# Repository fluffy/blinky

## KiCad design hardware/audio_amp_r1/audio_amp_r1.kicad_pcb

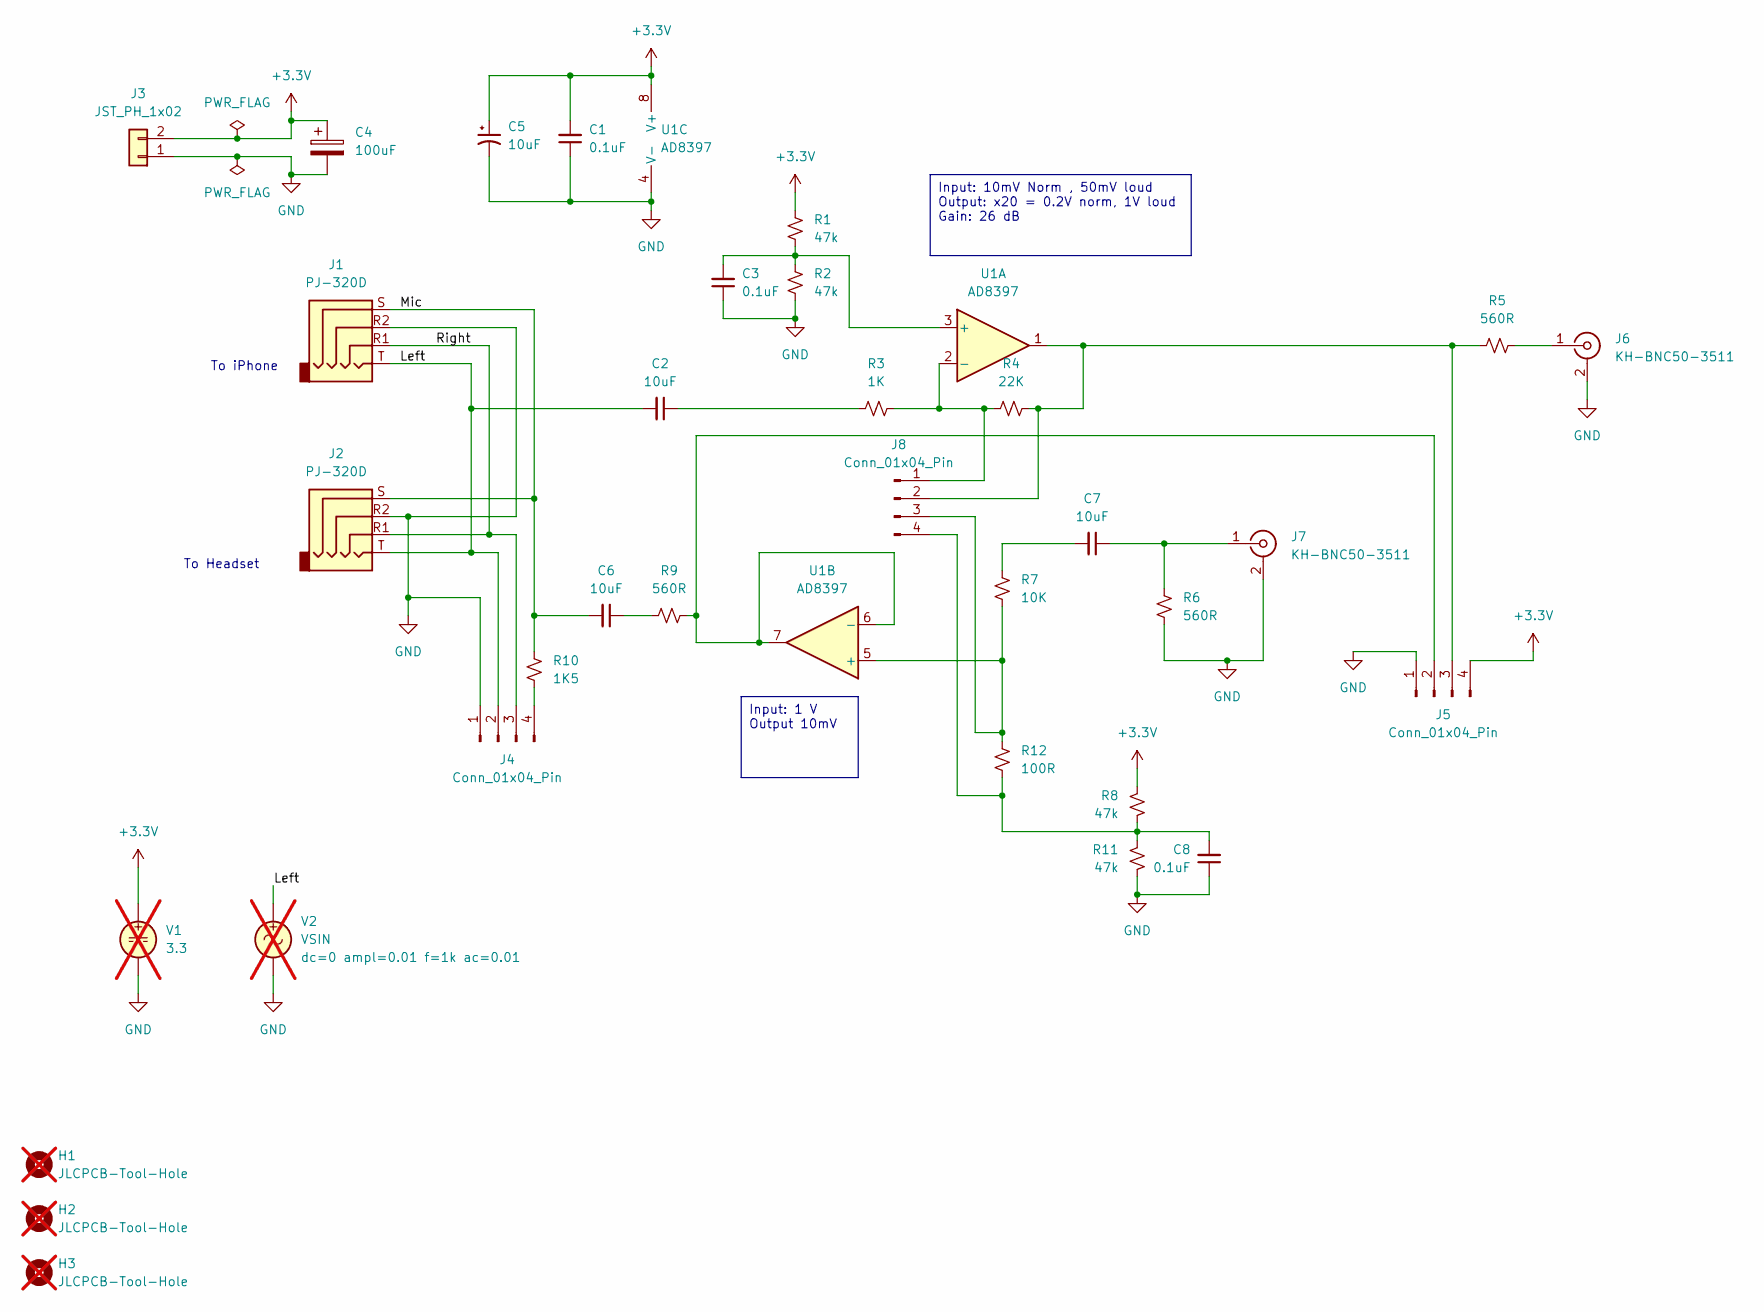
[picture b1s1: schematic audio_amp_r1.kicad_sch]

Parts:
C1, C3, C8: 0.1uF; C_0805_2012Metric; JLCPCB Part # C49678
C2, C6, C7: 10uF; C_0805_2012Metric; JLCPCB Part # C15850
C4: 100uF; CP_EIA-3528-21_Kemet-B; JLCPCB Part # C16133
C5: 10uF; CP_EIA-3216-18_Kemet-A; JLCPCB Part # C7171
H1, H2, H3: JLCPCB-Tool-Hole; MountingHole_JLCPCB_Tool; not fitted
J1, J2: PJ-320D; Jack_3.5mm_PJ320D_Horizontal-CJ; MPN PJ-320D; JLCPCB Part # C431535
J3: JST_PH_1x02; JST_PH_S2B-PH-SM4-TB_1x02-1MP_P2.00mm_Horizontal; JLCPCB Part # C295747
J4, J5, J8: Conn_01x04_Pin; PinHeader_1x04_P2.54mm_Vertical_SMD_Pin1Left; JLCPCB Part # C2883761
J6, J7: KH-BNC50-3511; BNC_Amphenol_B6252HB-NPP3G-50_Horizontal-CJ; MPN KH-BNC50-3511; JLCPCB Part # C2837587
R1, R2, R8, R11: 47k; R_0805_2012Metric; JLCPCB Part # C17713
R3: 1K; R_0805_2012Metric; JLCPCB Part # C17513
R4: 22K; R_0805_2012Metric; JLCPCB Part # C17560
R5, R6, R9: 560R; R_0805_2012Metric; JLCPCB Part # C28636
R7: 10K; R_0805_2012Metric; JLCPCB Part # C17414
R10: 1K5; R_0805_2012Metric; JLCPCB Part # C4310
R12: 100R; R_0805_2012Metric; JLCPCB Part # C17408
U1: AD8397; SOIC-8_3.9x4.9mm_P1.27mm; JLCPCB Part # C578714
V1: 3.3; not fitted
V2: VSIN; not fitted

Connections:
+3.3V: C1.2, C4.1, C5.1, J3.2, J5.4, R1.2, R8.2, U1.8 (V+), V1.1
/Left: C2.2, J1.T, J2.T, J4.2, V2.1
/Mic: C6.2, J1.S, J2.S, R10.2
/Right: J1.R1, J2.R1, J4.3
GND: C1.1, C3.1, C4.2, C5.2, C8.1, J1.R2, J2.R2, J3.1, J4.1, J5.1, J6.2 (Ext), J7.2 (Ext), R2.1, R6.2, R11.1, U1.4 (V-), V1.2, V2.2
unnamed: C2.1, R3.2
unnamed: C6.1, R9.1
unnamed: C7.2, R7.1
unnamed: J4.4, R10.1
unnamed: J5.2, R9.2, U1.6 (-), U1.7
unnamed: J5.3, J8.2, R4.1, R5.2, U1.1
unnamed: J6.1 (In), R5.1
unnamed: C7.1, J7.1 (In), R6.1
unnamed: J8.1, R3.1, R4.2, U1.2 (-)
unnamed: J8.3, R7.2, R12.1, U1.5 (+)
unnamed: C8.2, J8.4, R8.1, R11.2, R12.2
unnamed: C3.2, R1.1, R2.2, U1.3 (+)

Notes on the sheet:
Input: 1 V Output 10mV
Input: 10mV Norm , 50mV loud Output: x20 = 0.2V norm, 1V loud Gain: 26 dB
To iPhone
To Headset

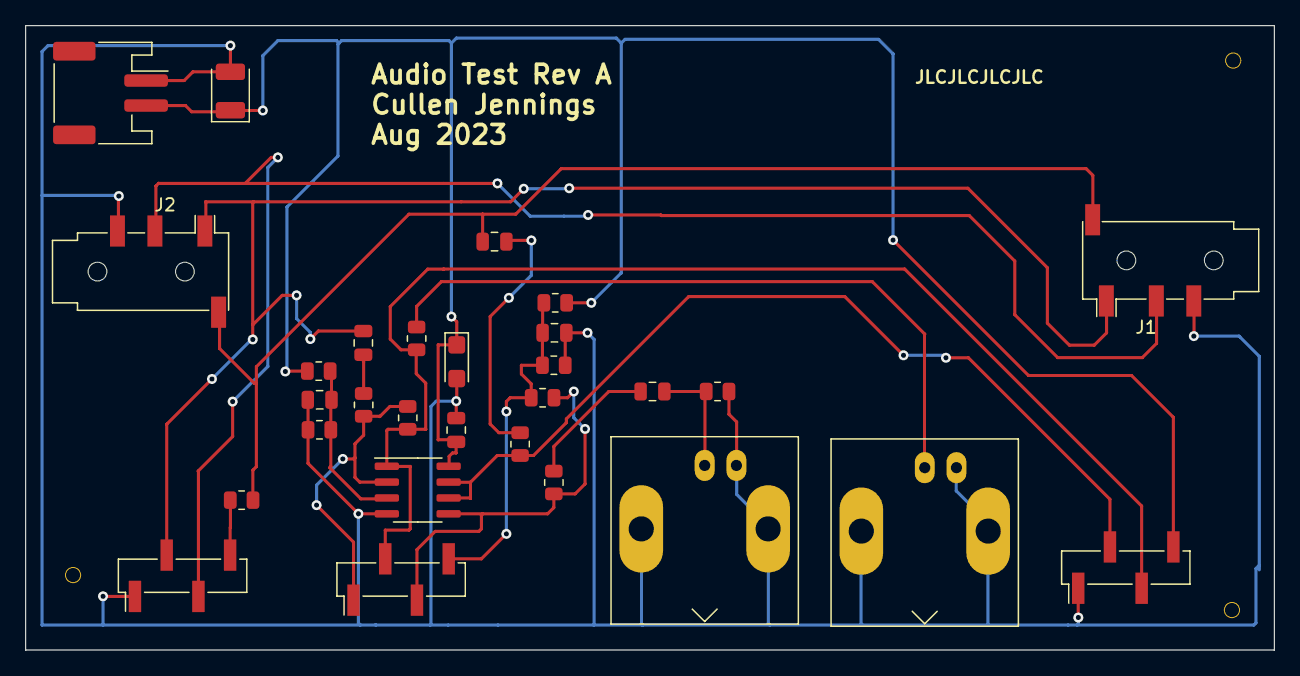
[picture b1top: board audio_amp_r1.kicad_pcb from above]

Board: 2 copper layers, 100.0 x 50.0 mm, 32 parts (0 on the bottom side), 17 nets.

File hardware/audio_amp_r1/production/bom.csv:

Designator,Footprint,Quantity,Value,LCSC Part #
"C1, C3, C8",0805,3,0.1uF,C49678
"C2, C6, C7",0805,3,10uF,C15850
C4,CP_EIA-3528-21_Kemet-B,1,100uF,C16133
C5,CP_EIA-3216-18_Kemet-A,1,10uF,C7171
"J1, J2",Jack_3.5mm_PJ320D_Horizontal-CJ,2,PJ-320D,C431535
J3,JST_PH_S2B-PH-SM4-TB_1x02-1MP_P2.00mm_Horizontal,1,JST_PH_1x02,C295747
"J4, J5, J8",PinHeader_1x04_P2.54mm_Vertical_SMD_Pin1Left,3,Conn_01x04_Pin,C2883761
"J6, J7",BNC_Amphenol_B6252HB-NPP3G-50_Horizontal-CJ,2,KH-BNC50-3511,C2837587
"R1, R11, R2, R8",0805,4,47k,C17713
R10,0805,1,1K5,C4310
R12,0805,1,100R,C17408
R3,0805,1,1K,C17513
R4,0805,1,22K,C17560
"R5, R6, R9",0805,3,560R,C28636
R7,0805,1,10K,C17414
U1,SOIC-8_3.9x4.9mm_P1.27mm,1,AD8397,C578714

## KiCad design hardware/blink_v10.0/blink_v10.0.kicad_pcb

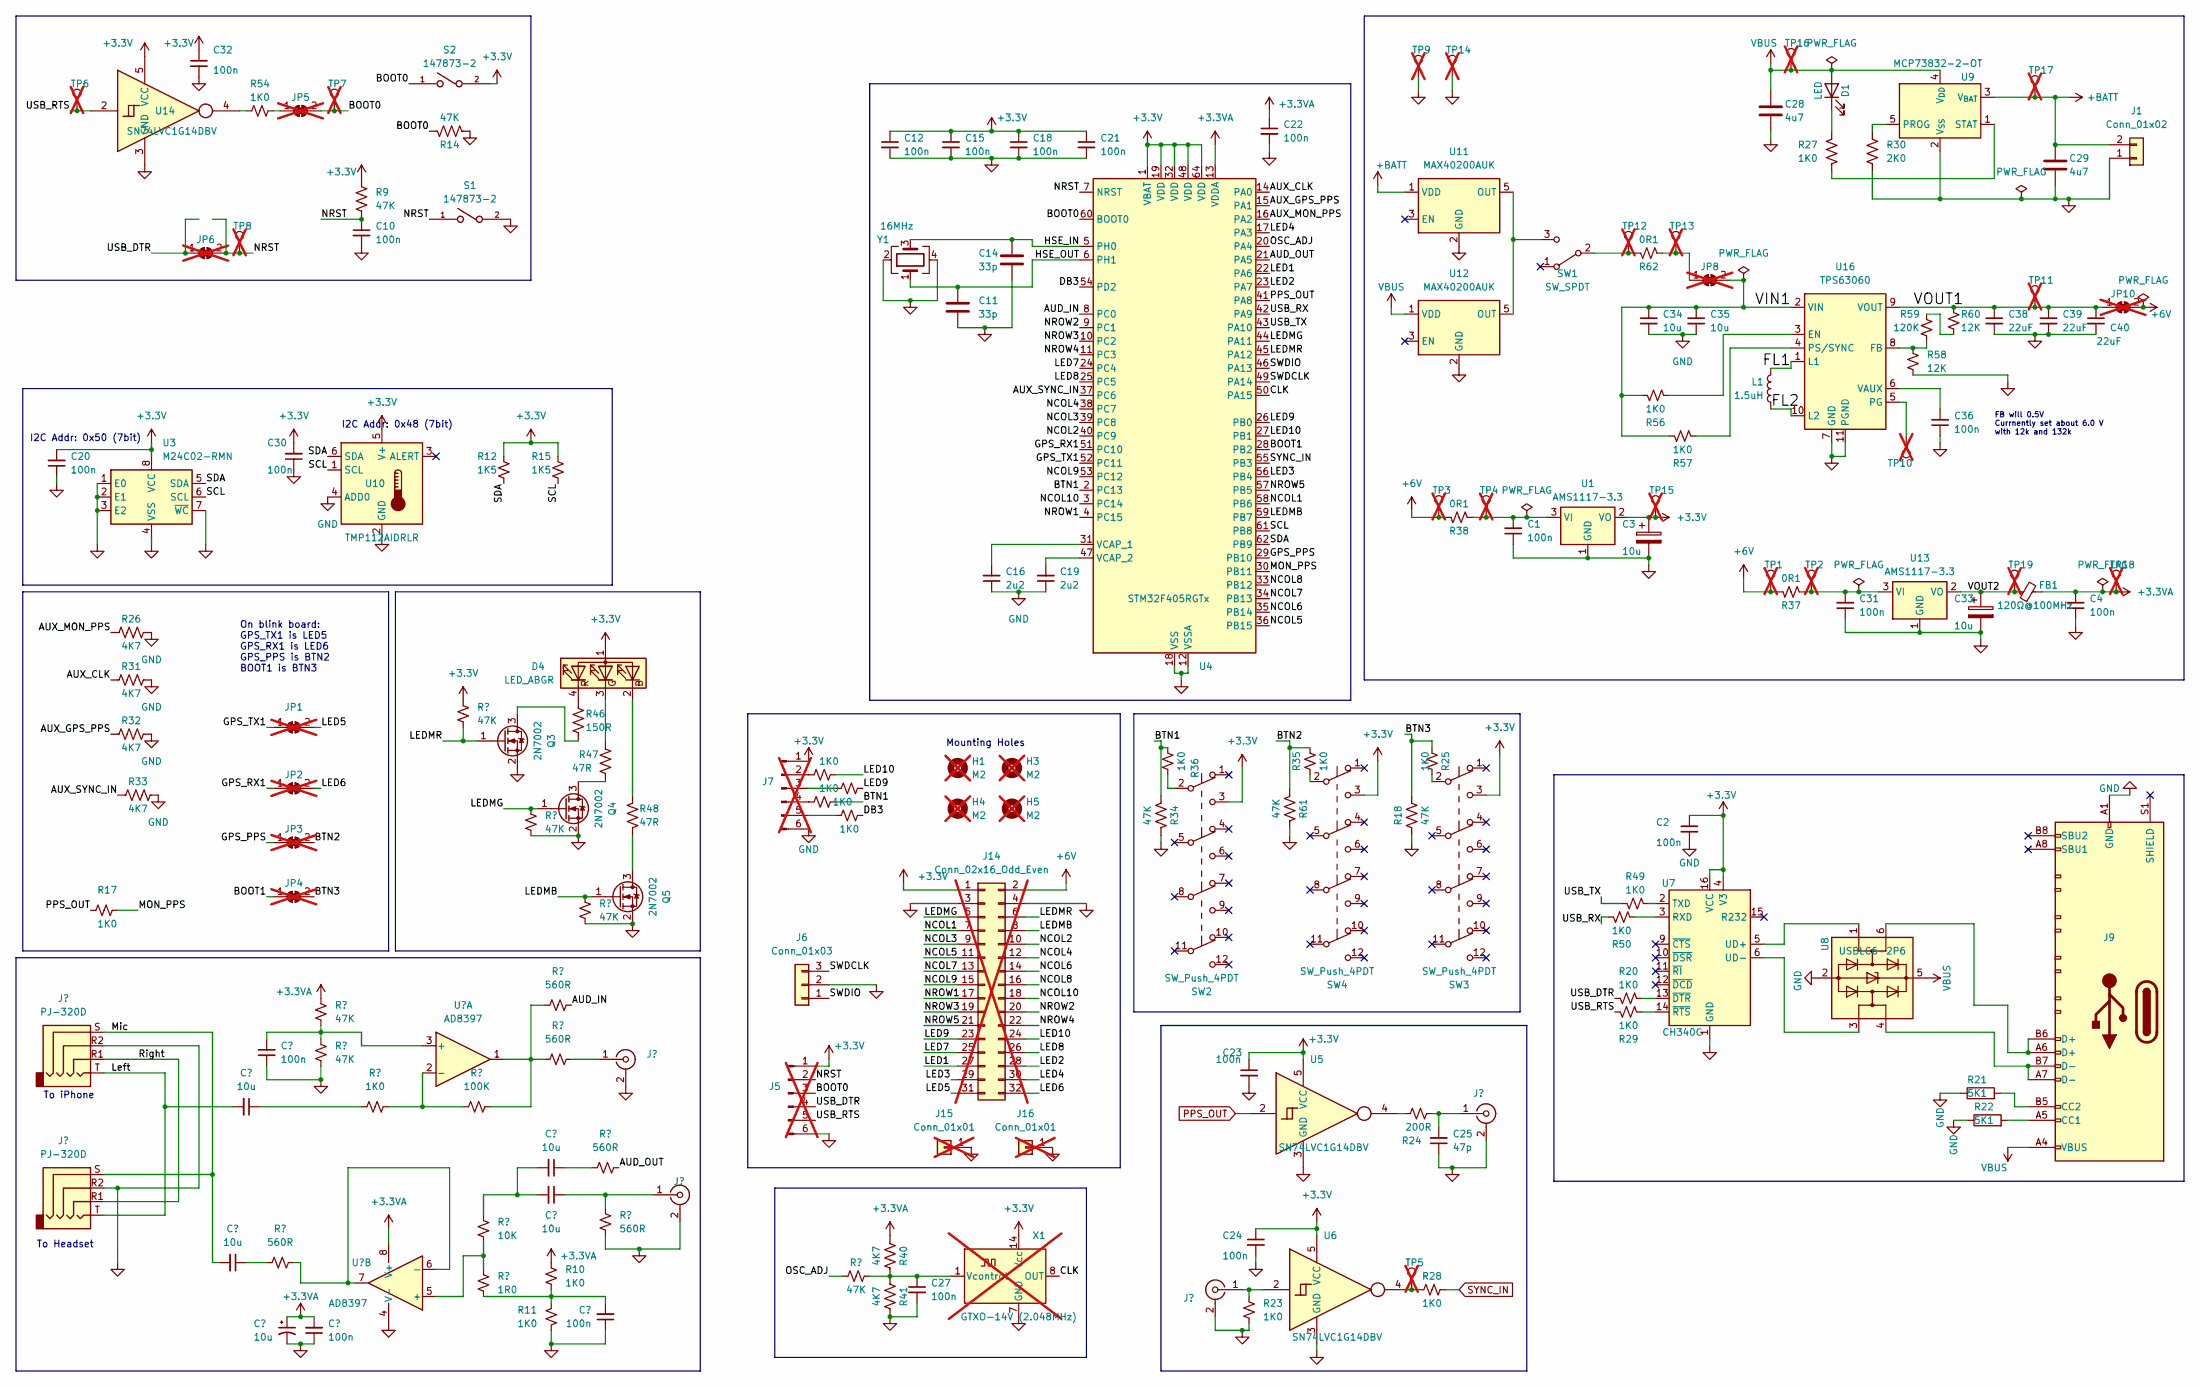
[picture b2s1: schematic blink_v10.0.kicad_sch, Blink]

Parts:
C1, C2, C12, C15, C18, C20, C21, C22, C23, C24, C30, C31, C32: 100n; C_0402_1005Metric; JLCPCB Part # C307331
C3, C5, C33: 10u; CP_EIA-3216-18_Kemet-A; JLCPCB Part # C7171
C4, C6, C9, C10, C17, C27, C36: 100n; C_0603_1608Metric; JLCPCB Part # C14663
C7, C8, C13, C26: 10u; C_0603_1608Metric; JLCPCB Part # C19702
C11, C14: 33p; C_0603_1608Metric; JLCPCB Part # C1663
C16, C19: 2u2; C_0603_1608Metric; JLCPCB Part # C23630
C25: 47p; C_0603_1608Metric; JLCPCB Part # C1671
C28, C29: 4u7; C_0603_1608Metric; JLCPCB Part # C19666
C34, C35: 10u; C_0603_1608Metric; JLCPCB Part # C96446
C38, C39, C40: 22uF; C_0805_2012Metric; JLCPCB Part # C45783
D1: LED; LED_0805_2012Metric; JLCPCB Part # C130114
D4: LED_ABGR; LED_RGB_MHS110FRGBCT; MPN MHS110FRGBCT; JLCPCB Part # C496820
FB1: 120Ω@100MHz; R_0603_1608Metric; JLCPCB Part # C127301
H1, H3, H4, H5: M2; MountingHole_2.2mm_M2; not fitted
J1: Conn_01x02; JST_PH_S2B-PH-SM4-TB_1x02-1MP_P2.00mm_Horizontal; JLCPCB Part # C295747
J2, J3: PJ-320D; Jack_3.5mm_PJ320D_Horizontal-CJ; MPN PJ-320D; JLCPCB Part # C431535
J4, J11, J12, J13: KH-BNC50-3511; BNC_Amphenol_B6252HB-NPP3G-50_Horizontal-CJ; MPN KH-BNC50-3511; JLCPCB Part # C2837587
J5, J7: Conn_01x06_Pin; PinHeader_1x06_P2.54mm_Vertical; not fitted
J6: Conn_01x03; JST_PH_S3B-PH-SM4-TB_1x03-1MP_P2.00mm_Horizontal; JLCPCB Part # C265101
J9: USB_C_Receptacle; USB_C_Receptacle_HRO_TYPE-C-31-M-12; JLCPCB Part # C165948
J14: Conn_02x16_Odd_Even; PinHeader_2x16_P2.54mm_Vertical; not fitted
J15, J16: Conn_01x01; PinSocket_1x01_P2.54mm_Vertical; not fitted
JP1, JP2, JP3, JP4: SolderJumper_2_Bridged; SolderJumper-2_P1.3mm_Bridged_RoundedPad1.0x1.5mm; not fitted
JP5, JP6, JP8, JP10: SolderJumper_2_Bridged; SolderJumper-2_P1.3mm_Bridged2Bar_RoundedPad1.0x1.5mm; not fitted
L1: 1.5uH; L_Coilcraft_XAL4020-XXX; MPN XFL4020-152MEC; JLCPCB Part # C3033018
Q3, Q4, Q5: 2N7002; SOT-23; JLCPCB Rotation Offset 180
R1, R2, R13, R16, R19: 560R; R_0603_1608Metric; JLCPCB Part # C23204
R3, R4, R9, R14, R18, R34, R39, R51, R52, R53, R61: 47K; R_0603_1608Metric; JLCPCB Part # C25819
R5, R10, R11, R17, R20, R23, R25, R27, R28, R29, R35, R36, R42, R43, R44, R45, R49, R50, R54, R56, R57: 1K0; R_0603_1608Metric; JLCPCB Part # C21190
R6: 10K; R_0603_1608Metric; JLCPCB Part # C25804
R7: 1R0; R_0603_1608Metric; JLCPCB Part # C22936
R8: 100K; R_0603_1608Metric; JLCPCB Part # C25803
R12, R15: 1K5; R_0603_1608Metric; JLCPCB Part # C22843
R21, R22: 5K1; R_0603_1608Metric; JLCPCB Part # C23186
R24: 200R; R_0603_1608Metric; JLCPCB Part # C8218
R26, R31, R32, R33, R40, R41: 4K7; R_0603_1608Metric; JLCPCB Part # C23162
R30: 2K0; R_0603_1608Metric; JLCPCB Part # C22975
R37, R38, R62: 0R1; R_1206_3216Metric; JLCPCB Part # C25334
R46: 150R; R_0603_1608Metric; JLCPCB Part # C22808
R47, R48: 47R; R_0603_1608Metric; JLCPCB Part # C23182
R58, R60: 12K; R_0603_1608Metric; JLCPCB Part # C22790
R59: 120K; R_0603_1608Metric; JLCPCB Part # C25808
S1, S2: 147873-2; SW_147873-2; JLCPCB Part # C266189
SW1: SW_SPDT; SW_E-Switch_EG1224_SPDT_Angled; JLCPCB Part # C273395
SW2, SW3, SW4: SW_Push_4PDT; PBH4UOANAGX; JLCPCB Part # C273424
TP1, TP2, TP3, TP4, TP12, TP13: TestPoint_THTPad_D1.0mm_Drill0.5mm; not fitted
TP5, TP6, TP7, TP8, TP9, TP10, TP11, TP14, TP15, TP16, TP17, TP18, TP19: TestPoint_THTPad_D1.5mm_Drill0.7mm; not fitted
U1, U13: AMS1117-3.3; SOT-223-3_TabPin2; JLCPCB Part # C6186
U2: AD8397; SOIC-8_3.9x4.9mm_P1.27mm; JLCPCB Part # C578714
U3: M24C02-RMN; SOIC-8_3.9x4.9mm_P1.27mm; JLCPCB Part # C83836
U4: STM32F405RGTx; LQFP-64_10x10mm_P0.5mm; JLCPCB Part # C15742
U5, U6: SN74LVC1G14DBV; SOT-23-5; JLCPCB Part # C133145
U7: CH340C; SOIC-16_3.9x9.9mm_P1.27mm; JLCPCB Part # C84681
U8: USBLC6-2P6; SOT-666; JLCPCB Part # C2827693
U9: MCP73832-2-OT; SOT-23-5; JLCPCB Part # C424093
U10: TMP112AIDRLR; SOT-563; JLCPCB Part # C28927
U11, U12: MAX40200AUK; SOT-23-5; JLCPCB Part # C2649430
U14: SN74LVC1G14DBV; SOT-23-5; JLCPCB Rotation Offset 180
U16: TPS63060; Texas_S-PWSON-N10_ThermalVias; JLCPCB Part # C48567
X1: GTXO-14V (2.048MHz); OSC_DIP-14; MPN ACVTX1018A-2.048MHZ-D10; not fitted
Y1: 16MHz; Crystal_SMD_3225-4Pin_3.2x2.5mm; JLCPCB Part # C13738

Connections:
+3.3V: C2.1, C3.1, C12.1, C15.1, C18.1, C20.2, C21.1, C23.1, C24.1, C30.2, C32.1, D4.1 (A), J5.1, J7.1, J14.1, R9.1, R12.1, R15.1, R51.2, S2.2, SW2.3 (C), SW3.3 (C), SW4.3 (C), TP15.1, U1.2 (VO), U3.8 (VCC), U4.1 (VBAT), U4.19 (VDD), U4.32 (VDD), U4.48 (VDD), U4.64 (VDD), U5.5 (VCC), U6.5 (VCC), U7.4 (V3), U7.16 (VCC), U10.5 (V+), U14.5 (VCC), X1.14 (Vcc)
+3.3VA: C4.2, C5.1, C6.2, C22.1, FB1.2, R3.2, R10.1, R40.1, TP18.1, U2.8 (V+), U4.13 (VDDA)
+6V: J14.2, JP10.2 (B), R37.2, R38.2, TP1.1, TP3.1
+BATT: C29.1, J1.2, TP17.1, U9.3 (V_{BAT}), U11.1 (VDD)
/AUD_IN: R1.1, U4.8 (PC0)
/AUD_OUT: R19.2, U4.21 (PA5)
/AUX_CLK: R31.1, U4.14 (PA0)
/AUX_GPS_PPS: R32.1, U4.15 (PA1)
/AUX_MON_PPS: R26.1, U4.16 (PA2)
/AUX_SYNC_IN: R33.1, U4.37 (PC6)
/BOOT0: J5.3, JP5.2 (B), R14.1, S2.1, TP7.1, U4.60 (BOOT0)
/BOOT1: JP4.1 (A), U4.28 (PB2)
/BTN1: R34.2, R36.2, R44.1, U4.2 (PC13)
/BTN2: JP3.2 (B), R35.2, R61.2
/BTN3: JP4.2 (B), R18.2, R25.2
/CLK: U4.50 (PA15), X1.8 (OUT)
/DB3: R45.1, U4.54 (PD2)
/FL1: L1.1, U16.1 (L1)
/FL2: L1.2, U16.10 (L2)
/GPS_PPS: JP3.1 (A), U4.29 (PB10)
/GPS_RX1: JP2.1 (A), U4.51 (PC10)
/GPS_TX1: JP1.1 (A), U4.52 (PC11)
/HSE_IN: C14.1, U4.5 (PH0), Y1.3
/HSE_OUT: C11.1, U4.6 (PH1), Y1.1
/LED1: J14.27, U4.22 (PA6)
/LED2: J14.28, U4.23 (PA7)
/LED3: J14.29, U4.56 (PB4)
/LED4: J14.30, U4.17 (PA3)
/LED5: J14.31, JP1.2 (B)
/LED6: J14.32, JP2.2 (B)
/LED7: J14.25, U4.24 (PC4)
/LED8: J14.26, U4.25 (PC5)
/LED9: J14.23, R43.1, U4.26 (PB0)
/LED10: J14.24, R42.1, U4.27 (PB1)
/LEDMB: J14.8, Q5.1 (G), R53.2, U4.59 (PB7)
/LEDMG: J14.5, Q4.1 (G), R52.2, U4.44 (PA11)
/LEDMR: J14.6, Q3.1 (G), R51.1, U4.45 (PA12)
/Left: C8.2, J2.T, J3.T
/MON_PPS: R17.2, U4.30 (PB11)
/Mic: C7.2, J2.S, J3.S
/NCOL1: J14.7, U4.58 (PB6)
/NCOL2: J14.10, U4.40 (PC9)
/NCOL3: J14.9, U4.39 (PC8)
/NCOL4: J14.12, U4.38 (PC7)
/NCOL5: J14.11, U4.36 (PB15)
/NCOL6: J14.14, U4.35 (PB14)
/NCOL7: J14.13, U4.34 (PB13)
/NCOL8: J14.16, U4.33 (PB12)
/NCOL9: J14.15, U4.53 (PC12)
/NCOL10: J14.18, U4.3 (PC14)
/NROW1: J14.17, U4.4 (PC15)
/NROW2: J14.20, U4.9 (PC1)
/NROW3: J14.19, U4.10 (PC2)
/NROW4: J14.22, U4.11 (PC3)
/NROW5: J14.21, U4.57 (PB5)
/NRST: C10.1, J5.2, JP6.2 (B), R9.2, S1.1, TP8.1, U4.7 (NRST)
/OSC_ADJ: R39.2, U4.20 (PA4)
/Right: J2.R1, J3.R1
/SCL: R15.2, U3.6 (SCL), U4.61 (PB8), U10.1 (SCL)
/SDA: R12.2, U3.5 (SDA), U4.62 (PB9), U10.6 (SDA)
/SWDCLK: J6.3, U4.49 (PA14)
/SWDIO: J6.1, U4.46 (PA13)
/USB_DTR: J5.4, JP6.1 (A), R20.2
/USB_RTS: J5.5, R29.1, TP6.1, U14.2
/USB_RX: R50.1, U4.42 (PA9)
/USB_TX: R49.2, U4.43 (PA10)
/VIN1: C34.1, C35.1, JP8.2 (B), R56.1, R57.1, U16.2 (VIN)
/VOUT1: C38.1, C39.1, C40.1, JP10.1 (A), R60.1, TP11.1, U16.9 (VOUT)
/VOUT2: C33.1, FB1.1, TP19.1, U13.2 (VO)
GND: C1.1, C2.2, C3.2, C4.1, C5.2, C6.1, C9.1, C10.2, C11.2, C12.2, C14.2, C15.2, C16.1, C17.1, C18.2, C19.1, C20.1, C21.2, C22.2, C23.2, C24.2, C25.1, C27.2, C28.2, C29.2, C30.1, C31.1, C32.2, C33.2, C34.2, C35.2, C36.1, C38.2, C39.2, C40.2, J1.1, J2.R2, J3.R2, J4.2 (Ext), J5.6, J6.2, J7.6, J9.A1 (GND), J9.A12 (GND), J9.B1 (GND), J9.B12 (GND), J11.2 (Ext), J12.2 (Ext), J13.2 (Ext), J14.3, J14.4, J15.1, J16.1, Q3.2 (S), Q4.2 (S), Q5.2 (S), R4.1, R11.2, R13.2, R14.2, R18.1, R21.1, R22.1, R23.2, R26.2, R30.2, R31.2, R32.2, R33.2, R34.1, R41.2, R52.1, R53.1, R58.2, R61.1, S1.2, TP9.1, TP14.1, U1.1 (GND), U2.4 (V-), U3.1 (E0), U3.2 (E1), U3.3 (E2), U3.4 (VSS), U3.7 (~WC), U4.12 (VSSA), U4.18 (VSS), U4.63 (VSS), U5.3 (GND), U6.3 (GND), U7.1 (GND), U8.2 (GND), U9.2 (V_{SS}), U10.2 (GND), U10.4 (ADD0), U11.2 (GND), U12.2 (GND), U13.1 (GND), U14.3 (GND), U16.7 (GND), U16.11 (PGND), X1.7 (GND), Y1.2, Y1.4
unnamed: C7.1, R2.1
unnamed: C8.1, R5.2
unnamed: C13.2, C26.2, R6.1
unnamed: C17.2, R7.2, R10.2, R11.1
unnamed: C26.1, R19.1
unnamed: D1.1 (K), R27.1
unnamed: D4.2 (BK), R48.1
unnamed: D4.3 (GK), R47.2
unnamed: D4.4 (RK), R46.2
unnamed: J4.1 (In), R23.1, U6.2
unnamed: J7.2, R42.2
unnamed: J7.3, R43.2
unnamed: J7.4, R44.2
unnamed: J7.5, R45.2
unnamed: J9.A5 (CC1), R22.2
unnamed: J9.B5 (CC2), R21.2
unnamed: J9.A6 (D+), J9.B6 (D+), U8.6 (I/O1)
unnamed: J9.A7 (D-), J9.B7 (D-), U8.4 (I/O2)
unnamed: C13.1, J11.1 (In), R13.1
unnamed: C25.2, J12.1 (In), R24.2
unnamed: J13.1 (In), R16.1
unnamed: JP5.1 (A), R54.2
unnamed: JP8.1 (A), R62.1, TP13.1
unnamed: Q3.3 (D), R46.1
unnamed: Q4.3 (D), R47.1
unnamed: Q5.3 (D), R48.2
unnamed: R1.2, R8.1, R16.2, U2.1
unnamed: R24.1, U5.4
unnamed: R25.1, SW3.2 (B)
unnamed: R28.2, TP5.1, U6.4
unnamed: R35.1, SW4.2 (B)
unnamed: R36.1, SW2.2 (B)
unnamed: R54.1, U14.4
unnamed: R59.1, R60.2
unnamed: R62.2, SW1.2 (B), TP12.1
unnamed: SW1.3 (C), U11.5 (OUT), U12.5 (OUT)
unnamed: C1.2, R38.1, TP4.1, U1.3 (VI)
unnamed: C9.2, R3.1, R4.2, U2.3 (+)
unnamed: R5.1, R8.2, U2.2 (-)
unnamed: R6.2, R7.1, U2.5 (+)
unnamed: R2.2, U2.6 (-), U2.7
unnamed: C16.2, U4.31 (VCAP_1)
unnamed: C19.2, U4.47 (VCAP_2)
unnamed: R50.2, U7.3 (RXD)
unnamed: R49.1, U7.2 (TXD)
unnamed: U7.5 (UD+), U8.1 (I/O1)
unnamed: U7.6 (UD-), U8.3 (I/O2)
unnamed: R20.1, U7.13 (~DTR)
unnamed: R29.2, U7.14 (~RTS)
unnamed: R30.1, U9.5 (PROG)
unnamed: R27.2, U9.1 (STAT)
unnamed: C31.2, R37.1, TP2.1, U13.3 (VI)
unnamed: R56.2, U16.3 (EN)
unnamed: R58.1, R59.2, U16.8 (FB)
unnamed: TP10.1, U16.5 (PG)
unnamed: R57.2, U16.4 (PS/SYNC)
unnamed: C36.2, U16.6 (VAUX)
unnamed: C27.1, R39.1, R40.2, R41.1, X1.1 (Vcontrol)
PPS_OUT: R17.1, U4.41 (PA8), U5.2
SYNC_IN: R28.1, U4.55 (PB3)
VBUS: C28.1, D1.2 (A), J9.A4 (VBUS), J9.A9 (VBUS), J9.B4 (VBUS), J9.B9 (VBUS), TP16.1, U8.5 (VBUS), U9.4 (V_{DD}), U12.1 (VDD)

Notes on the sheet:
I2C Addr: 0x48 (7bit)
FB will 0.5V Currnently set about 6.0 V with 12k and 132k
To iPhone
To Headset
I2C Addr: 0x50 (7bit)
Mounting Holes
On blink board: GPS_TX1 is LED5 GPS_RX1 is LED6 GPS_PPS is BTN2 BOOT1 is BTN3

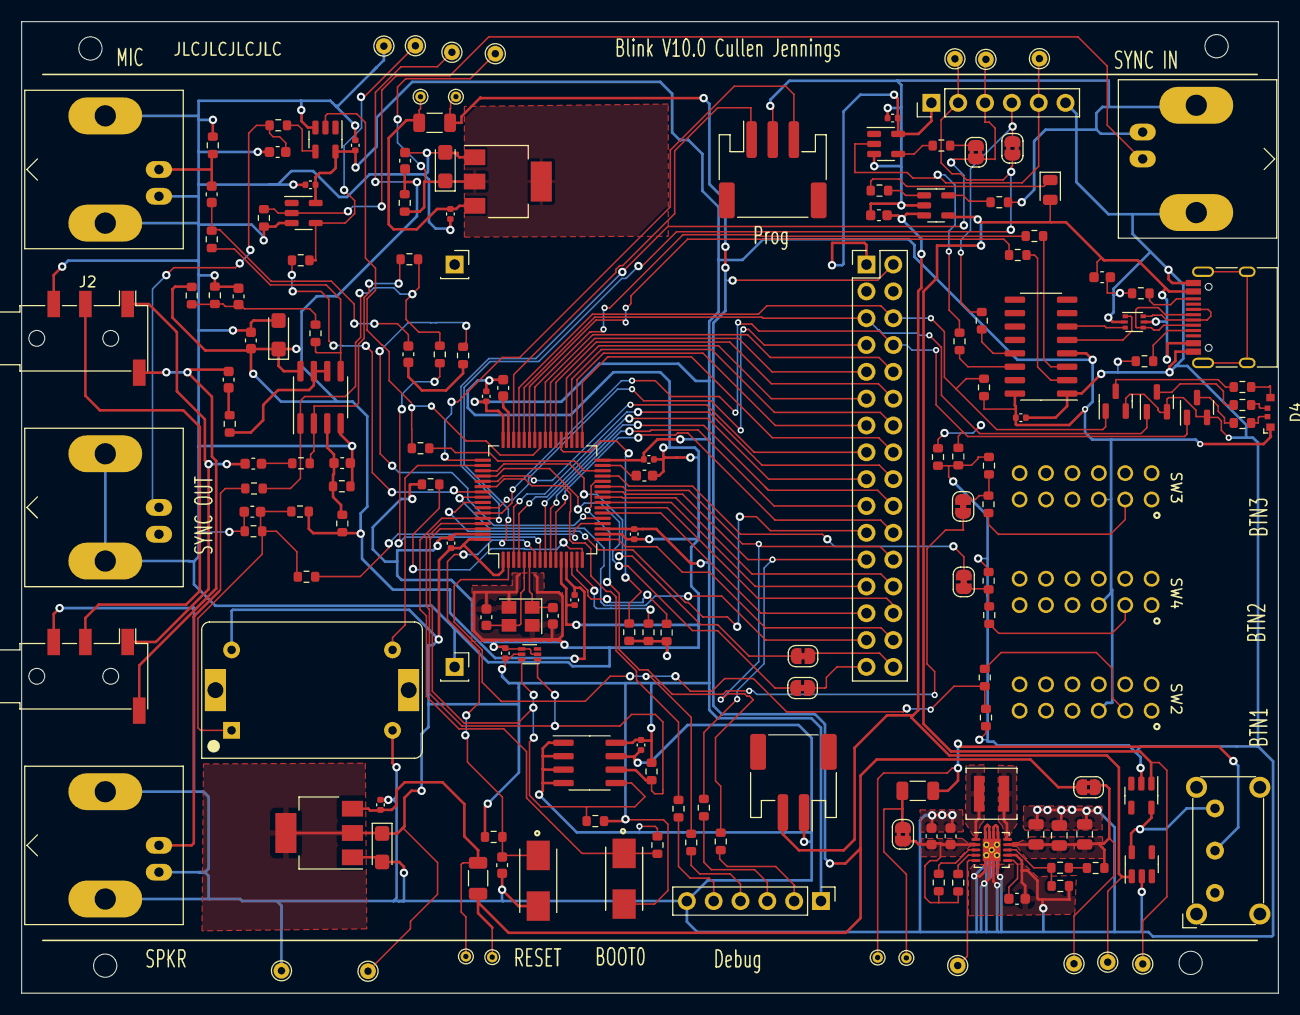
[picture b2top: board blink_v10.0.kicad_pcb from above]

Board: 2 copper layers, 119.0 x 92.0 mm, 175 parts (0 on the bottom side), 131 nets.

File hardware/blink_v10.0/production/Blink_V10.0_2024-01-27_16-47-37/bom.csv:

Designator,Footprint,Quantity,Value,LCSC Part #
"C1, C12, C15, C18, C2, C20, C21, C22, C23, C24, C30, C31, C32",0402,13,100n,C307331
"C10, C17, C27, C36, C4, C6, C9",0603,7,100n,C14663
"C11, C14",0603,2,33p,C1663
"C13, C26, C7, C8",0603,4,10u,C19702
"C16, C19",0603,2,2u2,C23630
C25,0603,1,47p,C1671
"C28, C29",0603,2,4u7,C19666
"C3, C33, C5",CP_EIA-3216-18_Kemet-A,3,10u,C7171
"C34, C35",0603,2,10u,C96446
"C38, C39, C40",0805,3,22uF,C45783
D1,0805,1,LED,C130114
D4,LED_RGB_MHS110FRGBCT,1,LED_ABGR,C496820
FB1,0603,1,120Ω@100MHz ,C127301
J1,JST_PH_S2B-PH-SM4-TB_1x02-1MP_P2.00mm_Horizontal,1,Conn_01x02,C295747
"J11, J12, J13, J4",BNC_Amphenol_B6252HB-NPP3G-50_Horizontal-CJ,4,KH-BNC50-3511,C2837587
"J2, J3",Jack_3.5mm_PJ320D_Horizontal-CJ,2,PJ-320D,C431535
J6,JST_PH_S3B-PH-SM4-TB_1x03-1MP_P2.00mm_Horizontal,1,Conn_01x03,C265101
J9,USB_C_Receptacle_HRO_TYPE-C-31-M-12,1,USB_C_Receptacle,C165948
L1,L_Coilcraft_XAL4020-XXX,1,1.5uH,C3033018
"Q3, Q4, Q5",SOT-23,3,2N7002,C8545
"R1, R13, R16, R19, R2",0603,5,560R,C23204
"R10, R11, R17, R20, R23, R25, R27, R28, R29, R35, R36, R42, R43, R44, R45, R49, R5, R50, R54, R56, R57",0603,21,1K0,C21190
"R12, R15",0603,2,1K5,C22843
"R14, R18, R3, R34, R39, R4, R51, R52, R53, R61, R9",0603,11,47K,C25819
"R21, R22",0603,2,5K1,C23186
R24,0603,1,200R,C8218
"R26, R31, R32, R33, R40, R41",0603,6,4K7,C23162
R30,0603,1,2K0,C22975
"R37, R38, R62",1206,3,0R1,C25334
R46,0603,1,150R,C22808
"R47, R48",0603,2,47R,C23182
"R58, R60",0603,2,12K,C22790
R59,0603,1,120K,C25808
R6,0603,1,10K,C25804
R7,0603,1,1R0,C22936
R8,0603,1,100K,C25803
"S1, S2",SW_147873-2,2,147873-2,C266189
SW1,SW_E-Switch_EG1224_SPDT_Angled,1,SW_SPDT,C273395
"SW2, SW3, SW4",PBH4UOANAGX,3,SW_Push_4PDT,C273424
"U1, U13",SOT-223-3_TabPin2,2,AMS1117-3.3,C6186
U10,SOT-563,1,TMP112AIDRLR,C28927
"U11, U12",SOT-23-5,2,MAX40200AUK,C2649430
"U14, U5, U6",SOT-23-5,3,SN74LVC1G14DBV,C133145
U16,Texas_S-PWSON-N10_ThermalVias,1,TPS63060,C48567
U2,SOIC-8_3.9x4.9mm_P1.27mm,1,AD8397,C578714
U3,SOIC-8_3.9x4.9mm_P1.27mm,1,M24C02-RMN,C83836
U4,LQFP-64_10x10mm_P0.5mm,1,STM32F405RGTx,C15742
U7,SOIC-16_3.9x9.9mm_P1.27mm,1,CH340C,C84681
U8,SOT-666,1,USBLC6-2P6,C2827693
U9,SOT-23-5,1,MCP73832-2-OT,C424093
Y1,Crystal_SMD_3225-4Pin_3.2x2.5mm,1,16MHz ,C13738
